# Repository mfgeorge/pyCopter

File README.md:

<h1>pyCopter </h1><br>
<br>
A multi-roter copter firmware written in micropython for a LoPy 
microcontroller (ESP32). The hardware designs used to make the flight 
control board will also be available on this repository. 
<br>
Contributers: <br>
<br>
Chad Bickel <br>
Michael George <br>
Oscar Ruiz <br>
<br>
<br>
File Hierachy:
<br>
resources - A folder containing links and references used throughout the 
project.
<br>
pyCopter_board - A folder containing the eagle hardware design files and 
bill of materials for the flight controller.
<br>
src - A folder containing the source code for the flight controller.
<br>
A project being performed in ME-507, California Polytechnic State 
University, San Luis Obispo

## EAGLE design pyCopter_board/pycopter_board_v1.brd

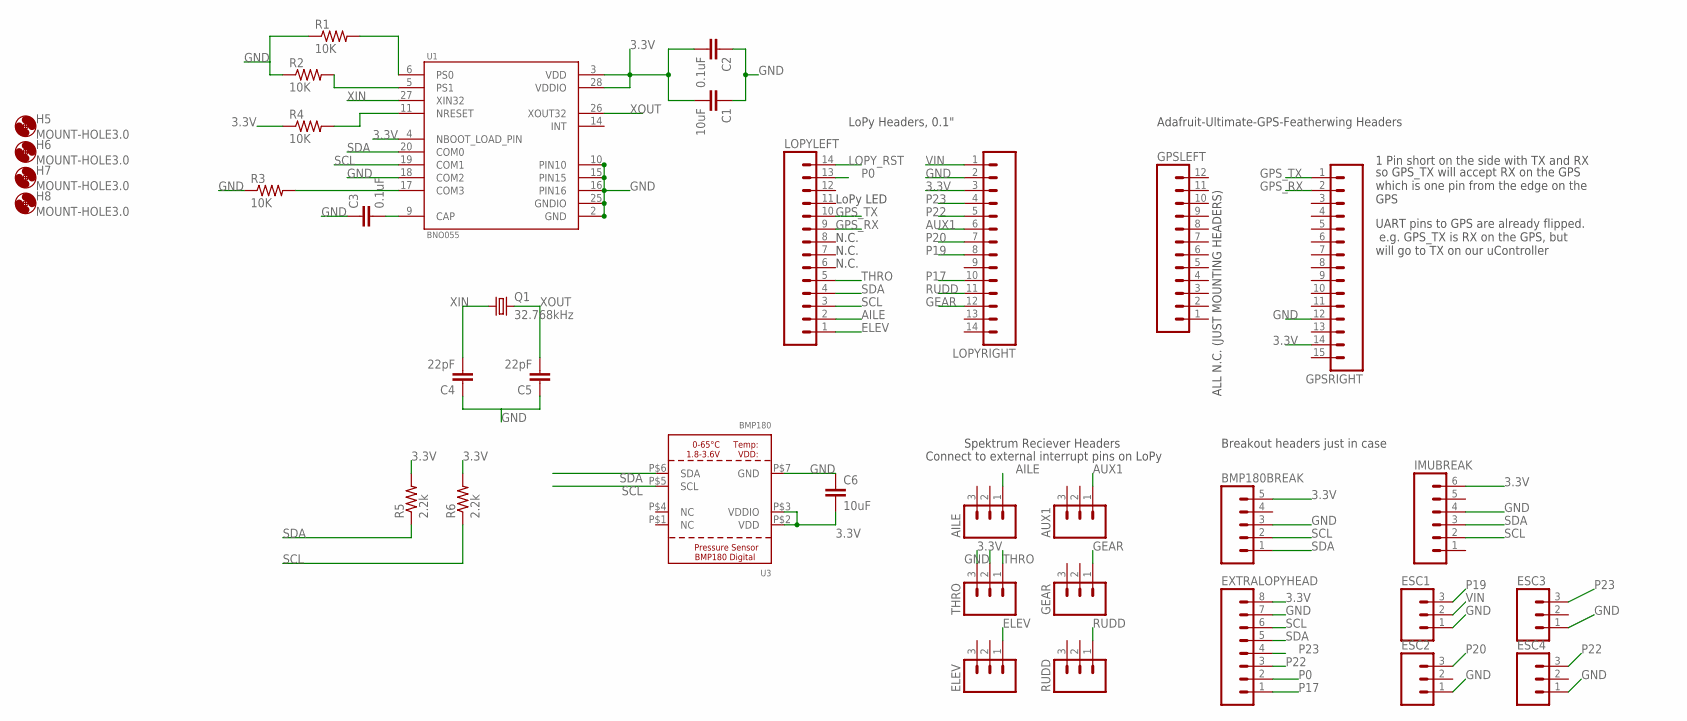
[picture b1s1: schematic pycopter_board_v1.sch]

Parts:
AILE: M03PTH; 1X03
AUX1: M03PTH; 1X03
BMP180BREAK: M05PTH; 1X05
C1, C6: 10uF; 0402-CAP
C2, C3: 0.1uF; 0402-CAP
C4, C5: 22pF; 0402-CAP
ELEV: M03PTH; 1X03
ESC1, ESC2, ESC3, ESC4: M03PTH; 1X03
EXTRALOPYHEAD: M08SILK_FEMALE_PTH; 1X08
GEAR: M03PTH; 1X03
GPSLEFT: M12PTH; 1X12
GPSRIGHT: M15; 1X15
H5, H6, H7, H8: MOUNT-HOLE3.0; 3,0
IMUBREAK: M06SILK_FEMALE_PTH; 1X06
LOPYLEFT: M14; 1X14
LOPYRIGHT: M14; 1X14
Q1: 32.768kHz; TC38H
R1, R2, R3, R4: 10K; 0402-RES
R5, R6: 2.2k; 0402-RES
RUDD: M03PTH; 1X03
THRO: M03PTH; 1X03
U1: BNO055; LGA28R50P4X10_380X520X100
U3: BMP180; BMP180_EXTENDED

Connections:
3.3V: BMP180BREAK.5, C1.2, C2.2, C6.2, EXTRALOPYHEAD.8, GPSRIGHT.14, IMUBREAK.6, LOPYRIGHT.3, R4.1, R5.2, R6.2, THRO.2, U1.3 (VDD), U1.4 (NBOOT_LOAD_PIN), U1.28 (VDDIO), U3.P$2 (VDD), U3.P$3 (VDDIO)
AILE: AILE.1, LOPYLEFT.2
AUX1: AUX1.1, LOPYRIGHT.6
ELEV: ELEV.1, LOPYLEFT.1
GEAR: GEAR.1, LOPYRIGHT.12
GND: BMP180BREAK.3, C1.1, C2.1, C3.1, C4.1, C5.1, C6.1, ESC1.1, ESC2.1, ESC3.1, ESC4.1, EXTRALOPYHEAD.7, GPSRIGHT.12, IMUBREAK.4, LOPYRIGHT.2, R1.1, R2.1, R3.1, THRO.3, U1.2 (GND), U1.10 (PIN10), U1.15 (PIN15), U1.16 (PIN16), U1.18 (COM2), U1.25 (GNDIO), U3.P$7 (GND)
GPS_RX: GPSRIGHT.2, LOPYLEFT.9
GPS_TX: GPSRIGHT.1, LOPYLEFT.10
LOPY_RST: LOPYLEFT.14
unnamed: C3.2, U1.9 (CAP)
unnamed: R3.2, U1.17 (COM3)
unnamed: R1.2, U1.6 (PS0)
unnamed: R2.2, U1.5 (PS1)
unnamed: R4.2, U1.11 (NRESET)
P0: EXTRALOPYHEAD.2, LOPYLEFT.13
P17: EXTRALOPYHEAD.1, LOPYRIGHT.10
P19: ESC1.3, LOPYRIGHT.8
P20: ESC2.3, LOPYRIGHT.7
P22: ESC4.3, EXTRALOPYHEAD.3, LOPYRIGHT.5
P23: ESC3.3, EXTRALOPYHEAD.4, LOPYRIGHT.4
RUDD: LOPYRIGHT.11, RUDD.1
SCL: BMP180BREAK.2, EXTRALOPYHEAD.6, IMUBREAK.2, LOPYLEFT.3, R6.1, U1.19 (COM1), U3.P$5 (SCL)
SDA: BMP180BREAK.1, EXTRALOPYHEAD.5, IMUBREAK.3, LOPYLEFT.4, R5.1, U1.20 (COM0), U3.P$6 (SDA)
THRO: LOPYLEFT.5, THRO.1
VIN: ESC1.2, LOPYRIGHT.1
XIN: C4.2, Q1.1, U1.27 (XIN32)
XOUT: C5.2, Q1.2, U1.26 (XOUT32)

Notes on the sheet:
LoPy Headers, 0.1"
Adafruit-Ultimate-GPS-Featherwing Headers
1 Pin short on the side with TX and RX
UART pins to GPS are already flipped. e.g. GPS_TX is RX on the GPS, but will go to TX on our uController
so GPS_TX will accept RX on the GPS which is one pin from the edge on the GPS
ALL N.C. (JUST MOUNTING HEADERS)
Spektrum Reciever Headers
Connect to external interrupt pins on LoPy
N.C.
LoPy LED
Breakout headers just in case

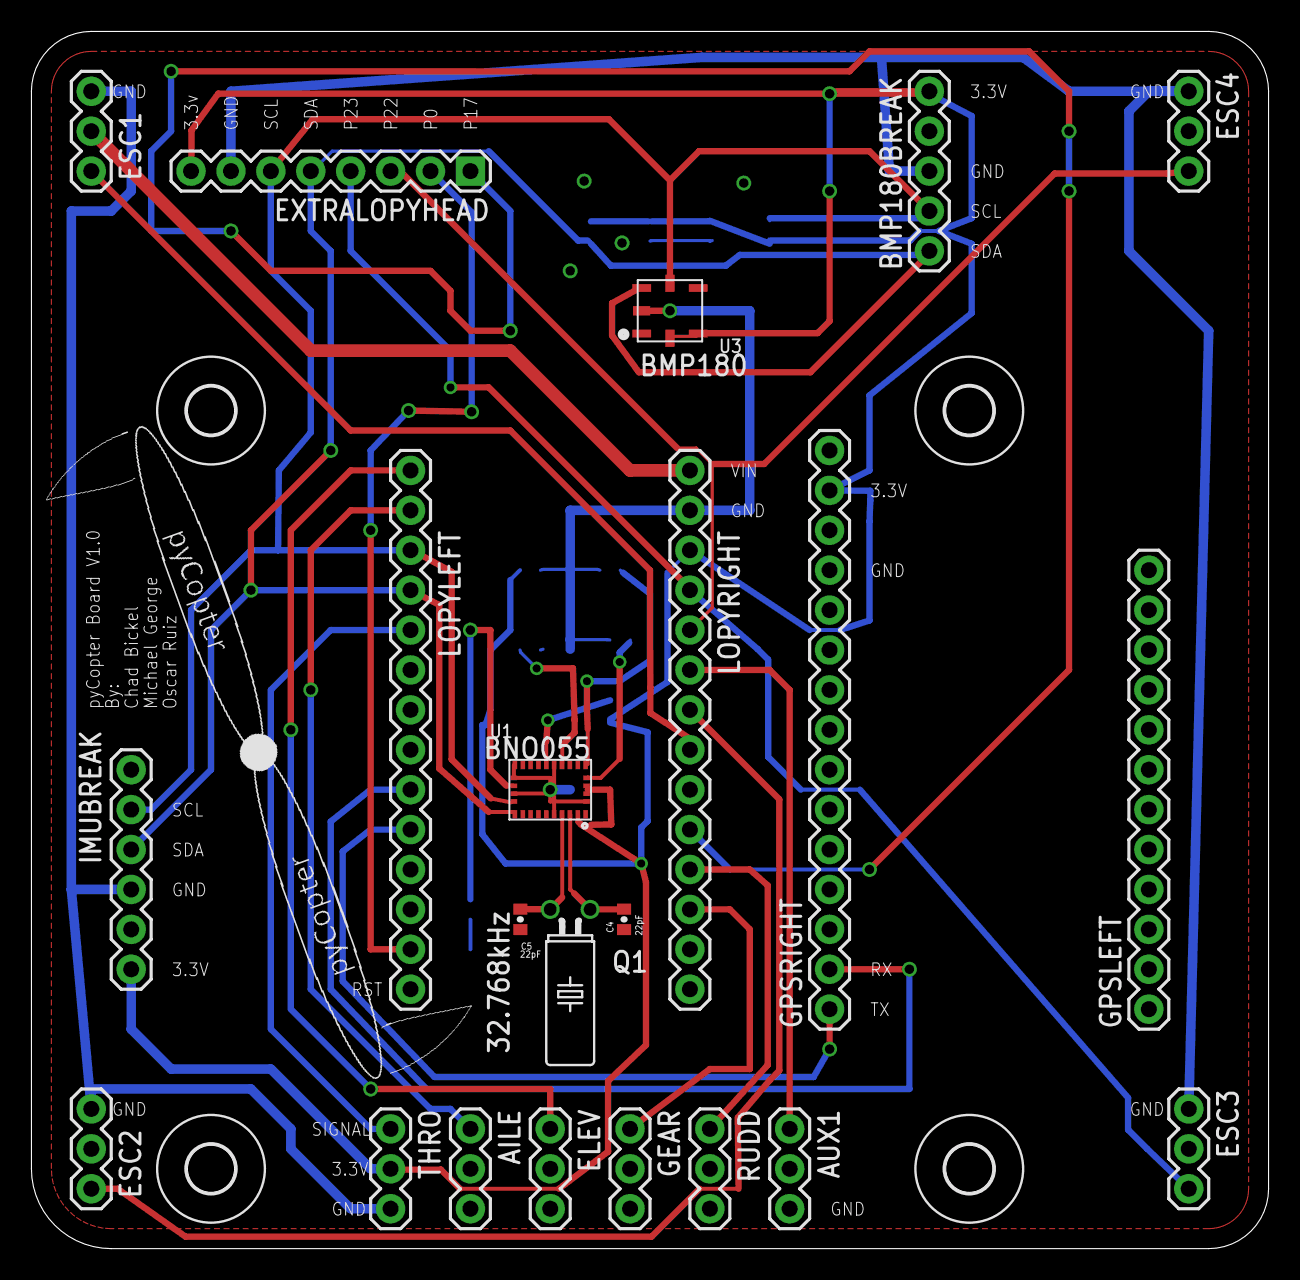
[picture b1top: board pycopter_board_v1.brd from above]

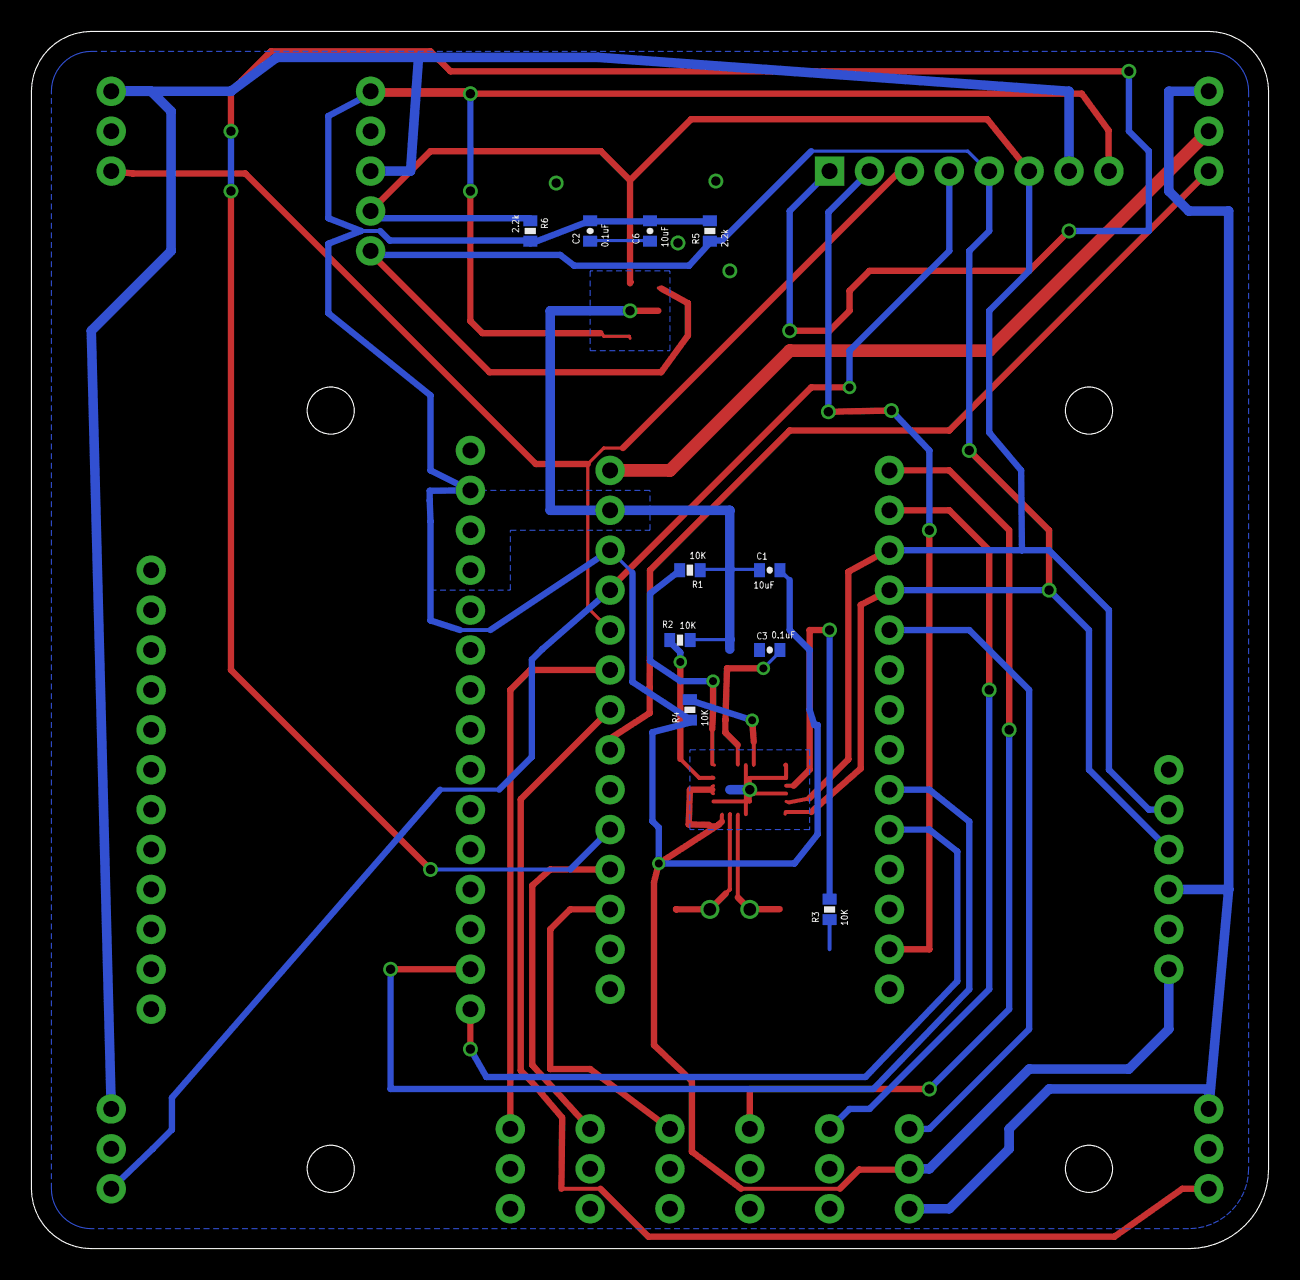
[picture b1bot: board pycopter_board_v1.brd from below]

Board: 2 copper layers, 78.7 x 77.5 mm, 36 parts (10 on the bottom side), 26 nets.

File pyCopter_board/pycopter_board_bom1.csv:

"Part";"Value";"Device";"Package";"Description";"AVAILABILITY";"DESCRIPTION";"MF";"MP";"MPN";"OC_FARNELL";"OC_NEWARK";"PACKAGE";"PRICE";"PROD_ID";
"AILE";"";"M03PTH";"1X03";"Header 3";"";"";"";"";"";"";"";"";"";"";
"AUX1";"";"M03PTH";"1X03";"Header 3";"";"";"";"";"";"";"";"";"";"";
"BMP180BREAK";"";"M05PTH";"1X05";"Header 5";"";"";"";"";"";"";"";"";"";"";
"C1";"10uF";"CAP0402-CAP";"0402-CAP";"Capacitor";"";"";"";"";"";"";"";"";"";"";
"C2";"0.1uF";"CAP0402-CAP";"0402-CAP";"Capacitor";"";"";"";"";"";"";"";"";"";"";
"C3";"0.1uF";"CAP0402-CAP";"0402-CAP";"Capacitor";"";"";"";"";"";"";"";"";"";"";
"C4";"22pF";"CAP0402-CAP";"0402-CAP";"Capacitor";"";"";"";"";"";"";"";"";"";"";
"C5";"22pF";"CAP0402-CAP";"0402-CAP";"Capacitor";"";"";"";"";"";"";"";"";"";"";
"C6";"10uF";"CAP0402-CAP";"0402-CAP";"Capacitor";"";"";"";"";"";"";"";"";"";"";
"ELEV";"";"M03PTH";"1X03";"Header 3";"";"";"";"";"";"";"";"";"";"";
"ESC1";"";"M03PTH";"1X03";"Header 3";"";"";"";"";"";"";"";"";"";"";
"ESC2";"";"M03PTH";"1X03";"Header 3";"";"";"";"";"";"";"";"";"";"";
"ESC3";"";"M03PTH";"1X03";"Header 3";"";"";"";"";"";"";"";"";"";"";
"ESC4";"";"M03PTH";"1X03";"Header 3";"";"";"";"";"";"";"";"";"";"";
"EXTRALOPYHEAD";"";"M08SILK_FEMALE_PTH";"1X08";"Header 8";"";"";"";"";"";"";"";"";"";"CONN-08438";
"GEAR";"";"M03PTH";"1X03";"Header 3";"";"";"";"";"";"";"";"";"";"";
"GPSLEFT";"";"M12PTH";"1X12";"Header 12";"";"";"";"";"";"";"";"";"";"";
"GPSRIGHT";"";"M15";"1X15";"Header 15";"";"";"";"";"";"";"";"";"";"";
"H5";"MOUNT-HOLE3.0";"MOUNT-HOLE3.0";"3,0";"MOUNTING HOLE with drill center marker";"";"";"";"";"";"";"";"";"";"";
"H6";"MOUNT-HOLE3.0";"MOUNT-HOLE3.0";"3,0";"MOUNTING HOLE with drill center marker";"";"";"";"";"";"";"";"";"";"";
"H7";"MOUNT-HOLE3.0";"MOUNT-HOLE3.0";"3,0";"MOUNTING HOLE with drill center marker";"";"";"";"";"";"";"";"";"";"";
"H8";"MOUNT-HOLE3.0";"MOUNT-HOLE3.0";"3,0";"MOUNTING HOLE with drill center marker";"";"";"";"";"";"";"";"";"";"";
"IMUBREAK";"";"M06SILK_FEMALE_PTH";"1X06";"Header 6";"";"";"";"";"";"";"";"";"";"CONN-08437";
"LOPYLEFT";"";"M14";"1X14";"Header 14";"";"";"";"";"";"";"";"";"";"";
"LOPYRIGHT";"";"M14";"1X14";"Header 14";"";"";"";"";"";"";"";"";"";"";
"Q1";"32.768kHz";"CRYSTALTC38H";"TC38H";"CRYSTAL";"";"";"";"";"";"unknown";"unknown";"";"";"";
"R1";"10K";"RESISTOR0402-RES";"0402-RES";"Resistor";"";"";"";"";"";"";"";"";"";"";
"R2";"10K";"RESISTOR0402-RES";"0402-RES";"Resistor";"";"";"";"";"";"";"";"";"";"";
"R3";"10K";"RESISTOR0402-RES";"0402-RES";"Resistor";"";"";"";"";"";"";"";"";"";"";
"R4";"10K";"RESISTOR0402-RES";"0402-RES";"Resistor";"";"";"";"";"";"";"";"";"";"";
"R5";"2.2k";"RESISTOR0402-RES";"0402-RES";"Resistor";"";"";"";"";"";"";"";"";"";"";
"R6";"2.2k";"RESISTOR0402-RES";"0402-RES";"Resistor";"";"";"";"";"";"";"";"";"";"";
"RUDD";"";"M03PTH";"1X03";"Header 3";"";"";"";"";"";"";"";"";"";"";
"THRO";"";"M03PTH";"1X03";"Header 3";"";"";"";"";"";"";"";"";"";"";
"U1";"BNO055";"BNO055";"LGA28R50P4X10_380X520X100";"BNO055 9-axis Absolute Orientation Sensor ( SiP ) w/Sensors and Sensor Fusion";"Good";"BNO055 9-axis Absolute Orientation Sensor ( SiP ) w/Sensors and Sensor Fusion";"Bosch";"BNO055";"";"";"";"LGA-28 Bosch";"9.48 USD";"";
"U3";"BMP180";"BMP180EXT";"BMP180_EXTENDED";"BMP180 Digital Pressure Sensor";"";"";"";"";"";"";"";"";"";"";

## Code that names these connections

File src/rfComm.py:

#!/bin/python
"""
..  module: rfComm
    :platform: micropython boards
    :synopsis: Module for an RF controller to control the quadcopter

..  topic:: Author

    Michael George

Module for containing the code necessary to communicate with an RF controller
receiver, such as the Spektrum DX 6.
"""

# Handle the case where we aren't in micropython for documentation
# generation
try:
    import machine
except ImportError:
    import sys
    # Add some dummy libraries
    sys.path.insert(0, '../dummy_libraries')
    from dummy_libraries import machine


class RFController6CH:
    """
    A generic parent class for a 6 channel radio module
    Lays out what needs to be implemented so that all controllers
    will implement the same methods, no matter what type they are.

    | All controller classes should implement at least these methods:
    """
    def __init__(self):
        raise NotImplementedError("Subclasses should implement this!")

    def get_thrust(self):
    	raise NotImplementedError("Subclasses should implement this!")

    def get_roll(self):
    	raise NotImplementedError("Subclasses should implement this!")

    def get_pitch(self):
    	raise NotImplementedError("Subclasses should implement this!")

    def get_yaw(self):
    	raise NotImplementedError("Subclasses should implement this!")

    def get_switch1(self):
    	raise NotImplementedError("Subclasses should implement this!")

    def get_switch2(self):
    	raise NotImplementedError("Subclasses should implement this!")

class SpektrumController(RFController6CH):
    """
    A class for a specific 6 channel Spektrum radio module.

    :param thro_pin: Pin that the thro connection is on
    :param aile_pin: Pin that the aile connection is on
    :param elev_pin: Pin that the elev connection is on
    :param rudd_pin: Pin that the rudd connection is on
    :param gear_pin: Pin that the gear connection is on
    :param aux1_pin: Pin that the aux1 connection is on
    """

    def __init__(self, thro_pin, aile_pin, elev_pin, rudd_pin, gear_pin, aux1_pin):
        """
        The constructor for the Spektrum Controller
        """
        # Make the servo pulse objects connected to the specified pins
        self.thro_pulse = ServoPulse(thro_pin)
        self.aile_pulse = ServoPulse(aile_pin)
        self.elev_pulse = ServoPulse(elev_pin)
        self.rudd_pulse = ServoPulse(rudd_pin)
        self.gear_pulse = ServoPulse(gear_pin)
        self.aux1_pulse = ServoPulse(aux1_pin)

        # Store last values so some filtering may be implemented in the
        # future
        self.last_thrust = 0
        self.last_roll = 0
        self.last_yaw = 0
        self.last_pitch = 0

    def get_thrust(self):
        """
        Gets the thrust value of the thrust signal being sent

        :return: thrust value on a 0-50 scale
        """
        value = (self.thro_pulse.get_width() - 1048)/(1933 - 1048)*50
        self.last_thrust = value
        return value

    def get_roll(self):
        """
        Gets the roll value of the roll signal being sent

        :return: roll value on a 0-50 scale
        """
        value = (self.aile_pulse.get_width() - 1094)/(1893 - 1094)*50-25
        self.last_roll = value
        return value 

    def get_pitch(self):
        """
        Gets the pitch value of the pitch signal being sent

        :return: pitch value on a 0-50 scale
        """
        value = (self.elev_pulse.get_width() - 1077)/(1876 - 1077)*50-25
        self.last_pitch = value
        return value 

    def get_yaw(self):
        """
        Gets the yaw value of the yaw signal being sent

        :return: Yaw value on a 0-50 scale
        """
        value = (self.rudd_pulse.get_width() - 1086)/(1876 - 1086)*50-25
        self.last_yaw = value
        return value 

    def get_switch1(self):
        """
        Gets the position of the 1st switch

        :return: 1 if the switch is on, 0 if it is off
        """
        value = 1 if self.gear_pulse.get_width() > 1500 else 0
        return value

    def get_switch2(self):
        """
        Gets the position of the 2nd switch

        :return: 1 if the switch is on, 0 if it is off
        """
        value = 1 if self.aux1_pulse.get_width() > 1500 else 0
        return value


class ServoPulse:
    """
    A servo_pulse Class written by wagnerc4 on github and modified by michael george for our
    purposes.

    :Changes Made:

        Instead of using IC interrupts here which limits the pin choice
        (trouble with timer 8 and 1 identified, may be others not working either)
        we use external interrupts so that this can be done on any pin, given they
        do not have the same CPU port NUMBER. ie PBn and PAn cannot both be used
        to measure servo pulses.

    The constructor parameters are:

    :param pin: Pin that the servo pulse is connected to.
    :param timer: Timer that can be used to mark the amount of time
        the pulse was high for.
    """

    #: Varible to hold information about the pulse timing
    start = width = last_width = 0

    def __init__(self, pin, timer=machine.Timer(8, prescaler=83, period=0xffff)):
        """
        Constructor for the ServoPulse class
        """
        self.pulseCounter = timer
        self.tickConversion = 1e6/(self.pulseCounter.freq()*self.pulseCounter.period())
        # input("Any key to continue configuring external interrupts")
        self.pin = pin
        self.interrupt = machine.ExtInt(self.pin, machine.ExtInt.IRQ_RISING_FALLING, machine.Pin.PULL_NONE, self.callback)
        self.interrupt.enable()
        print("External Interrupt Set up on Line: ", self.interrupt.line())

    #@micropython.native
    def callback(self, line):
        """
        Callback that the external interrupt will call

        :param line: The line that the interrupt is on always gets passed
            to the callback.
        """
        now = self.pulseCounter.counter()
        if self.pin.value(): 
            self.start = now
        else: 
            self.width = (now - self.start) & 0xffff

    #@micropython.native
    def get_width(self):
        """
        method for getting the most recent width of the last servo pulse

        :return: the width in useconds
        """
        self.interrupt.disable()
        w = self.width
        self.interrupt.enable()
        w *= self.tickConversion
        # print(w)
        self.last_width = w if w > 950 and w < 1950 else self.last_width
        return self.last_width

    def __del__(self):
        """
        Deconstructor for the servopulse class. ends the external interrupt
        associated with the servopulse object.
        """
        self.timer.deinit()
        self.interrupt.disable()

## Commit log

2016-10-01 First Motor Control Script
2016-10-02 Working motor_control
2016-10-02 Latest working motor control script
2016-10-03 added readme file back into repo. initial commit was erased upon a force push.
2016-10-03 Main and motor_control are ready!
2016-10-03 removed platform specific files and added there filetypes to the git ignore list. Platform specific files can be managed by the end user as needed, but should not be stored in this repository. These 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
2016-10-03 made some small mods to the main and motor control code so that speeds can input quickly and tested. We need to adjust the initial offset of about 0 to 15 so that there is no dead zone before the mot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
2016-10-03 made the input argument into a tuple so that the user can input 4 speeds for all motors as a tuple in order to run offset calibration for all motors and find the start point in a single go.
2016-10-05 rearranged the folder structure of our repo. added a resources and src folder and moved our source code into it. removed the pyboard readme from the repo, as this is an unecessary file.
2016-10-06 Added IMU library and changed main a bit
2016-10-07 added .gitattributes file for versioning the binary files associated with eagle.
2016-10-07 added two articles to the resources folder regarding the control of the quadcopter.
2016-10-07 Added old pyboard reference files
2016-10-07 Added simple motor control loop with IMU
2016-10-09 added rfComm to repo. Code is currently going down external interrupt route, however, I am reconsidering this now since external interrupts may slow down our processes significantly if we have 6 of t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
2016-10-10 finished up the code for the spektrum rf reciever. Ended up using the external interupt scheme of measuring pulse width. modeled the ServoPulse class off of another github project that implemented a 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
2016-10-10 added a bit in the main file so that the thrust of the reciever is put into the motor speeds.
2016-10-10 added another quadcopter project similar to ours into the resources folder.
2016-10-10 fixed the initial errors in the rfComm code. Now working on an OSError:16 thrown when an interrupt is not handeled.
2016-10-10 found the bug in the rfComm code that was reporting a pulse width of 0 for the throttle pin, and some others. It turns out that input capture interrupts are not currently working with timer 1 or 8. H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
2016-10-10 reconfigured servo pulse to work off of external interrupts. Now we can use any pins that do not have the same port number to measure the inputs from the rf reciever.
2016-10-10 finished the rfComm code. The conversion values from pulse width to servo speed may need a little more adjusting, but everything is close. The motors are now controlled by the thrust value coming fro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
2016-10-10 just changing a few comments.
2016-10-12 Added PID library file
2016-10-13 Added first iteration of schematic for custom board. The accelerometer was removed from the pyboard schematic.
2016-10-13 added a gps NMEA link to resources
2016-10-14 BMP180 lib ready
2016-10-15 modified README to reflect the new direction of our project.
2016-10-15 Update README.md
    fixed html in readme
2016-10-18 added two submodules in the resources directory for interfacing with the GPS. Updated rfComm to use the natural code emitter to speed up the interrupt callback twofold.
2016-10-19 added micropyGPS and MTK_command module copies to the src folder. If updated copies are needed, the resources folder still contains these as git submodules linked to their original repo.
2016-10-20 Added BNO055 chip library. Also started pyCopter board V1 in board folder. BNO055 connections are almost finished, just need to finish I2C connections.
2016-10-21 got the GPS fix on one satellite. wrote methods for a GPS class that uses the other GPS libraries. I would like to restructure this so that it is extending micropyGPS.
2016-10-21 Added pitch PID control to main. Trying to deal with OSError originating from i2c communication with the BNO055.
2016-10-21 moved around some files in order to save flash space on the pyboard.
2016-10-25 added a PID controller task which will manage all sub-control loops and fuse their outputs. Implemented into main. Not yet tested. May need to evaluate how using dictionaries impacts the control loop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
2016-10-26 Modified rfComm.py to disable interrupts during reading of variable shared with interrupt. Also added the the natural code emitter to the get_width function since it might run often enough. Updated .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
2016-10-26 Added BMP180 circuit and I2C circuit to schematic. LoPy connections are not complete yet
2016-10-27 Major Milestone - Setup offsets for the motor_controller to minimize dead zones - Fixed errors in the controller_task.py. - Implemented pitch, yaw, and roll controllers - Tested controllers to ensure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
2016-10-28 Testing BMP180
2016-10-28 modified the pyboard design to include the adafruit ultimate gps module. dropped down some headers for the spektrum transciever module.
2016-11-02 added gps tx and rx connections to LoPy board, began determining the pin definitions of LoPy board.
2016-11-03 Added boarded files
2016-11-03 Updated board
2016-11-03 modified .gitignore so that the .s# and .b# files are not included in the repository.
2016-11-03 added ground plane and made ESCs into triple headers.
2016-11-04 started adding traces to board. Added all GND traces and VIN traces. Working on 3.3v now.
2016-11-04 board is all connected as is. Will try for another version in the morning which has more components on the bottom.
2016-11-04 at a good base point for autorouter. The power traces are all thicker, and routed the all the radio transmitter pins to the outside of the LoPy.
2016-11-04 added a large ground layer after the fact to what should be the final board revision. just need to add rounded edges for the dimensions.
2016-11-04 changed the dimension of the board to have rounded corners. Now giving fonts and silkscreen some attention.
2016-11-04 made all of the fonts a pleasurable size and ratio. Also vectorized all of the fonts.
2016-11-04 changed all the values to be on the names layer so that they will be on the silkscreen by default.
2016-11-04 Added pycopter logo pictures
2016-11-04 made traces wider and added a top ground plane at the suggestion of charlie. also added text labels around the header pins.
2016-11-05 added some more updates based upon charlie's suggestions.
2016-11-05 Added logo to board
2016-11-05 removed all of the session files from the pycopter_board folder. these should no longer be added and are in the .gitignore.
2016-11-05 added the final v1.0 board version in a zip file that was sent to John Barry for production at OSHPark.
2016-11-05 added the official lopy pin out png to the resources folder.]
2016-11-09 New Boot.py
2016-11-10 Machine version of the BMP libarary
2016-11-10 initially added task_manager module. Refactoring the initial module now to make more generic, with better intent expressed in the code.
2016-11-12 Refactored TaskManager to accept tasks and manage them. added a test case to test the task manager and it's intended functionality.
2016-11-12 added more documentation comments to the task_manager.py module.
2016-11-14 refactored main file to use new task scheme. modified ProtectedData to be able to use some container and numeric operatos. refactored the names of task modules to make it more apparent what they are.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
2016-11-14 added bill of materials for the pycopter board to the board folder.
2016-11-17 Wrote a servo library since machine doesn't have one. Updated main and tried to get rid of the pyb library. Also commented out calibration of motor library
2016-11-17 Added a test folder
2016-11-18 added print statements for debugging to the bmp180.py in test
2016-11-23 modified the boot file. After some testing, and firmware upgrade, i2c communication is working. Not much modification done, except for trying twice to grab the i2c device if the resource is not avail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
2016-11-24 Started servo library. Should have basic functionality
2016-11-27 small changes to the bmp180 library to not print the debug messages. Added push_code.py- a tool to use when pushing directories filled with code to the LoPy via ftp.
2016-12-01 Added server code file
2016-12-02 Added calibration function to servo_lib, untested
2016-12-02 socket server code now grabs the correct ip address by asking the WLAN object instead of hard code.
2016-12-02 Added calibration routine to motor control task
2016-12-03 major debugging due to the port from the pyboard to the lopy and finally getting main to run without syntax errors. Now the servo library needs some attention and we need to get the output to the mot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
2016-12-04 generalized the ground_control socket so that it can accept other commands with callbacks other than just the setpoint. put all of the parsing within the ground control socket class. added methods to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
2016-12-05 minor changes. trying to get the BNO055 driver working. running into issues. suspect that clock stretching is the cause.
2016-12-05 last attempt at getting the BNO to work over i2c, now switching to UART.
2016-12-06 UART TEST
2016-12-06 made a uart test program which echos what it receives over uart.
2016-12-06 Added Pyboard I2C hack script
2016-12-07 successfully programmed a library for the BNO that uses UART instead of i2c
2016-12-07 small changes to the test program so that the o that the printing looks nicer.
2016-12-07 added the BNO datasheet to resources
2016-12-07 we are back at the stage where we were with the pyboard, but with a ground control task and saturation block on the control loop task. Had to implement dropping erroneous readings in get_yaw_rate as 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
2016-12-09 added sphinx files for generating documentation. started experimenting with sphinx. Added ground control code that is based on the position of playstation controller joystick positions, as well as a 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
2016-12-10 added some timing prints in main. Started pycopter's source code documentation. Task manager is done.
2016-12-10 renamed docs source and build folders to docs-source and docs-build in the repo root. changed the import on main so that there is no import error (since not in uPython) and so that documentation can 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
2016-12-10 the scheme for the documentation is sphinxapi now. Each module had a .rst file auto-generated which should include its members.
2016-12-10 altered libraries so that sphinx does not throw import errors when trying to import micropython only libraries. Acheived this by adding a dummy libraries module with a bunch of placeholder classes.
2016-12-11 added docstrings and comments to many files for the purpose of sphinx documentation.
2016-12-11 Comments added to the BMP library
2016-12-11 Commented BMP Library
2016-12-11 added some extra comments to the rfcomm module and a few others.
2016-12-11 motor_control task is commented
2016-12-11 added the ps_socket script to the documentation.
2016-12-11 Added documentation to BNO055 and servo libraries
2016-12-11 added comments to the push_code.py and a few extra to other files. Included push_code.py into the documentation.
2016-12-12 Added modified author
2016-12-12 Fixed typo in conf.py file
2016-12-12 added pitch logging, tuned the gains with 1/2 of the copter to a flyable point, added the tested data of the tuning, adjusted the ground control socket to send just a constant thrust level for tuning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
2016-12-12 Added Matlab data analysis file. Pictures from each plot will be added next
2016-12-12 Added tuning pictures

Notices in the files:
parts and their libraries:
SparkFun-Passives: Licensing: Creative Commons ShareAlike 4.0 International - https://creativecommons.org/licenses/by-sa/4.0
